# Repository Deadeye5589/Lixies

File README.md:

# Lixies
LED based Nixie style displays in different sizes

Based on the works of Connor Nishijima

A Lixie Clock consits of 4 or 6 units in either small or big version. An ESP8266 or ESP32 in combination with a DS3213 real time clock.

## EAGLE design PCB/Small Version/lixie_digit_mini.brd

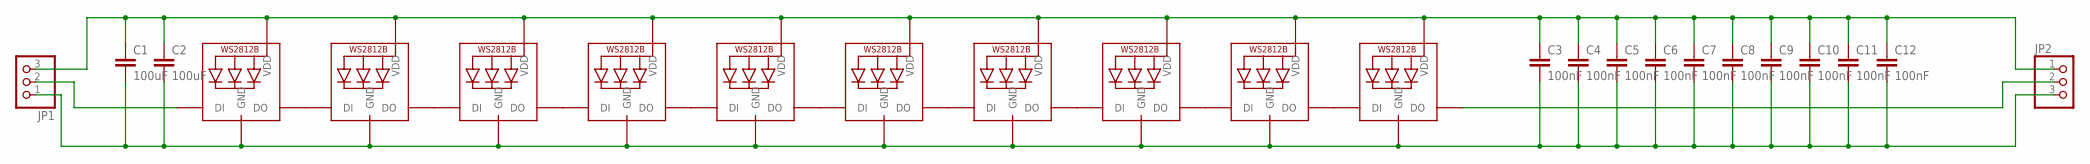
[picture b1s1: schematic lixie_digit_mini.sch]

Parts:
C1, C2: 100uF; C1206K
C3, C4, C5, C6, C7, C8, C9, C10, C11, C12: 100nF; C0805K
JP1, JP2: PINHD-1X3; 1X03
LED1, LED2, LED3, LED4, LED5, LED6, LED7, LED8, LED9, LED10: WS2812B5050; WS2812B

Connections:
GND: C1.2, C2.2, C3.2, C4.2, C5.2, C6.2, C7.2, C8.2, C9.2, C10.2, C11.2, C12.2, JP1.1, JP2.3, LED1.3-GND (GND), LED2.3-GND (GND), LED3.3-GND (GND), LED4.3-GND (GND), LED5.3-GND (GND), LED6.3-GND (GND), LED7.3-GND (GND), LED8.3-GND (GND), LED9.3-GND (GND), LED10.3-GND (GND)
unnamed: LED1.2-DOUT (DO), LED2.4-DIN (DI)
unnamed: LED2.2-DOUT (DO), LED3.4-DIN (DI)
unnamed: LED3.2-DOUT (DO), LED4.4-DIN (DI)
unnamed: LED4.2-DOUT (DO), LED5.4-DIN (DI)
unnamed: LED5.2-DOUT (DO), LED6.4-DIN (DI)
unnamed: LED6.2-DOUT (DO), LED7.4-DIN (DI)
unnamed: LED7.2-DOUT (DO), LED8.4-DIN (DI)
unnamed: LED8.2-DOUT (DO), LED9.4-DIN (DI)
unnamed: LED9.2-DOUT (DO), LED10.4-DIN (DI)
unnamed: JP1.2, LED1.4-DIN (DI)
unnamed: JP2.2, LED10.2-DOUT (DO)
VCC: C1.1, C2.1, C3.1, C4.1, C5.1, C6.1, C7.1, C8.1, C9.1, C10.1, C11.1, C12.1, JP1.3, JP2.1, LED1.1-VDD (VDD), LED2.1-VDD (VDD), LED3.1-VDD (VDD), LED4.1-VDD (VDD), LED5.1-VDD (VDD), LED6.1-VDD (VDD), LED7.1-VDD (VDD), LED8.1-VDD (VDD), LED9.1-VDD (VDD), LED10.1-VDD (VDD)

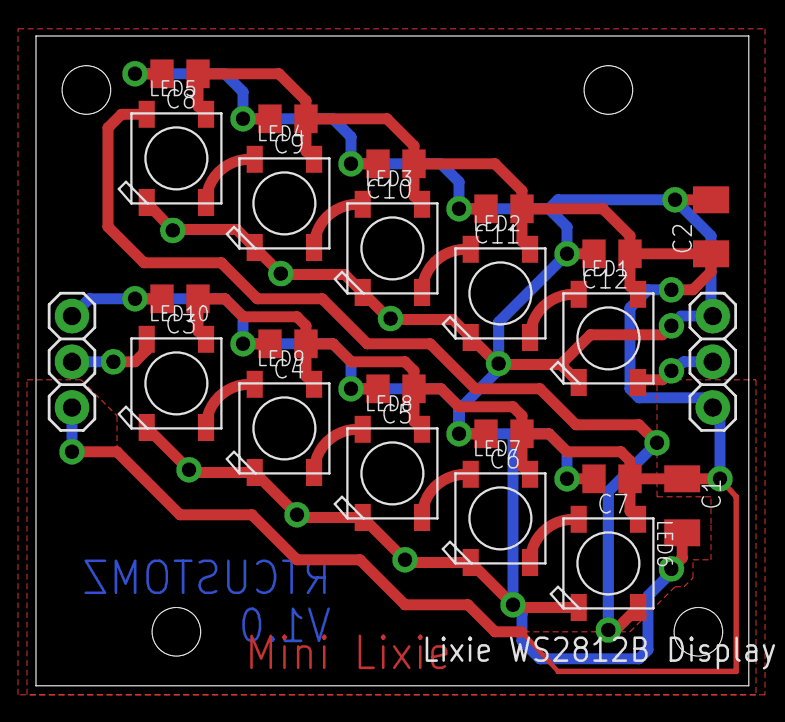
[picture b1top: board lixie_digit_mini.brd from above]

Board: 2 copper layers, 39.6 x 36.1 mm, 24 parts (0 on the bottom side), 13 nets.

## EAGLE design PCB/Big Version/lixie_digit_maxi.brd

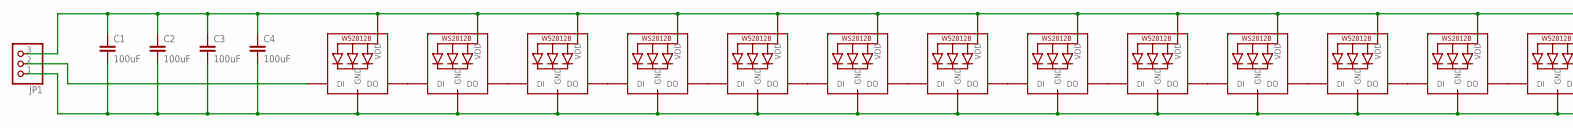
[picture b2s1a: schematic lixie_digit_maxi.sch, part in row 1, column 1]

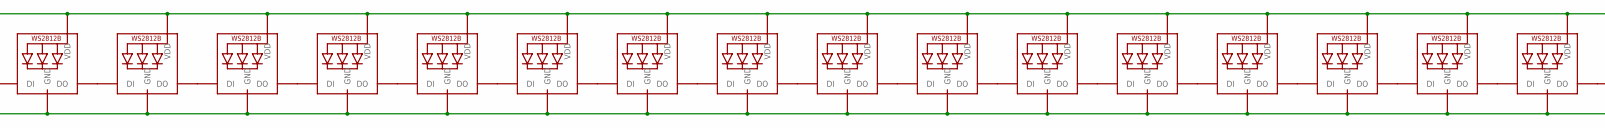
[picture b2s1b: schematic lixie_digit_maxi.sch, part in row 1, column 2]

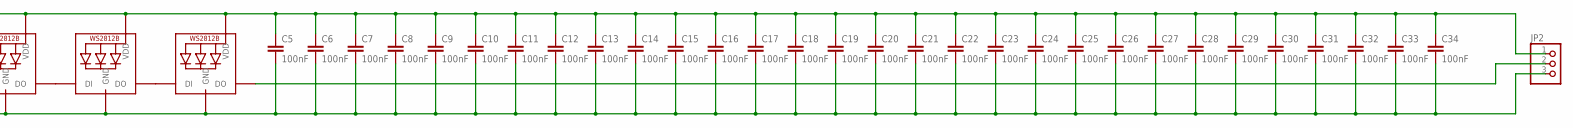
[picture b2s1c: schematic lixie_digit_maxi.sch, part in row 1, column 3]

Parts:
C1, C2, C3, C4: 100uF; C1206K
C5, C6, C7, C8, C9, C10, C11, C12, C13, C14, C15, C16, C17, C18, C19, C20, C21, C22, C23, C24, C25, C26, C27, C28, C29, C30, C31, C32, C33, C34: 100nF; C0402K
JP1, JP2: PINHD-1X3; 1X03
LED1, LED2, LED3, LED4, LED5, LED6, LED7, LED8, LED9, LED10, LED11, LED12, LED13, LED14, LED15, LED16, LED17, LED18, LED19, LED20, LED21, LED22, LED23, LED24, LED25, LED26, LED27, LED28, LED29, LED30: WS2812B5050; WS2812B

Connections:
GND: C1.2, C2.2, C3.2, C4.2, C5.2, C6.2, C7.2, C8.2, C9.2, C10.2, C11.2, C12.2, C13.2, C14.2, C15.2, C16.2, C17.2, C18.2, C19.2, C20.2, C21.2, C22.2, C23.2, C24.2, C25.2, C26.2, C27.2, C28.2, C29.2, C30.2, C31.2, C32.2, C33.2, C34.2, JP1.1, JP2.3, LED1.3-GND (GND), LED2.3-GND (GND), LED3.3-GND (GND), LED4.3-GND (GND), LED5.3-GND (GND), LED6.3-GND (GND), LED7.3-GND (GND), LED8.3-GND (GND), LED9.3-GND (GND), LED10.3-GND (GND), LED11.3-GND (GND), LED12.3-GND (GND), LED13.3-GND (GND), LED14.3-GND (GND), LED15.3-GND (GND), LED16.3-GND (GND), LED17.3-GND (GND), LED18.3-GND (GND), LED19.3-GND (GND), LED20.3-GND (GND), LED21.3-GND (GND), LED22.3-GND (GND), LED23.3-GND (GND), LED24.3-GND (GND), LED25.3-GND (GND), LED26.3-GND (GND), LED27.3-GND (GND), LED28.3-GND (GND), LED29.3-GND (GND), LED30.3-GND (GND)
unnamed: LED11.2-DOUT (DO), LED12.4-DIN (DI)
unnamed: LED12.2-DOUT (DO), LED13.4-DIN (DI)
unnamed: LED13.2-DOUT (DO), LED14.4-DIN (DI)
unnamed: LED14.2-DOUT (DO), LED15.4-DIN (DI)
unnamed: LED15.2-DOUT (DO), LED16.4-DIN (DI)
unnamed: LED16.2-DOUT (DO), LED17.4-DIN (DI)
unnamed: LED17.2-DOUT (DO), LED18.4-DIN (DI)
unnamed: LED18.2-DOUT (DO), LED19.4-DIN (DI)
unnamed: LED19.2-DOUT (DO), LED20.4-DIN (DI)
unnamed: LED20.2-DOUT (DO), LED21.4-DIN (DI)
unnamed: LED21.2-DOUT (DO), LED22.4-DIN (DI)
unnamed: LED22.2-DOUT (DO), LED23.4-DIN (DI)
unnamed: LED23.2-DOUT (DO), LED24.4-DIN (DI)
unnamed: LED24.2-DOUT (DO), LED25.4-DIN (DI)
unnamed: LED25.2-DOUT (DO), LED26.4-DIN (DI)
unnamed: LED26.2-DOUT (DO), LED27.4-DIN (DI)
unnamed: LED27.2-DOUT (DO), LED28.4-DIN (DI)
unnamed: LED28.2-DOUT (DO), LED29.4-DIN (DI)
unnamed: LED29.2-DOUT (DO), LED30.4-DIN (DI)
unnamed: LED10.2-DOUT (DO), LED11.4-DIN (DI)
unnamed: LED7.2-DOUT (DO), LED8.4-DIN (DI)
unnamed: LED6.2-DOUT (DO), LED7.4-DIN (DI)
unnamed: JP2.2, LED30.2-DOUT (DO)
unnamed: LED5.2-DOUT (DO), LED6.4-DIN (DI)
unnamed: LED3.2-DOUT (DO), LED4.4-DIN (DI)
unnamed: LED2.2-DOUT (DO), LED3.4-DIN (DI)
unnamed: LED1.2-DOUT (DO), LED2.4-DIN (DI)
unnamed: LED4.2-DOUT (DO), LED5.4-DIN (DI)
unnamed: LED8.2-DOUT (DO), LED9.4-DIN (DI)
unnamed: LED9.2-DOUT (DO), LED10.4-DIN (DI)
unnamed: JP1.2, LED1.4-DIN (DI)
VCC: C1.1, C2.1, C3.1, C4.1, C5.1, C6.1, C7.1, C8.1, C9.1, C10.1, C11.1, C12.1, C13.1, C14.1, C15.1, C16.1, C17.1, C18.1, C19.1, C20.1, C21.1, C22.1, C23.1, C24.1, C25.1, C26.1, C27.1, C28.1, C29.1, C30.1, C31.1, C32.1, C33.1, C34.1, JP1.3, JP2.1, LED1.1-VDD (VDD), LED2.1-VDD (VDD), LED3.1-VDD (VDD), LED4.1-VDD (VDD), LED5.1-VDD (VDD), LED6.1-VDD (VDD), LED7.1-VDD (VDD), LED8.1-VDD (VDD), LED9.1-VDD (VDD), LED10.1-VDD (VDD), LED11.1-VDD (VDD), LED12.1-VDD (VDD), LED13.1-VDD (VDD), LED14.1-VDD (VDD), LED15.1-VDD (VDD), LED16.1-VDD (VDD), LED17.1-VDD (VDD), LED18.1-VDD (VDD), LED19.1-VDD (VDD), LED20.1-VDD (VDD), LED21.1-VDD (VDD), LED22.1-VDD (VDD), LED23.1-VDD (VDD), LED24.1-VDD (VDD), LED25.1-VDD (VDD), LED26.1-VDD (VDD), LED27.1-VDD (VDD), LED28.1-VDD (VDD), LED29.1-VDD (VDD), LED30.1-VDD (VDD)

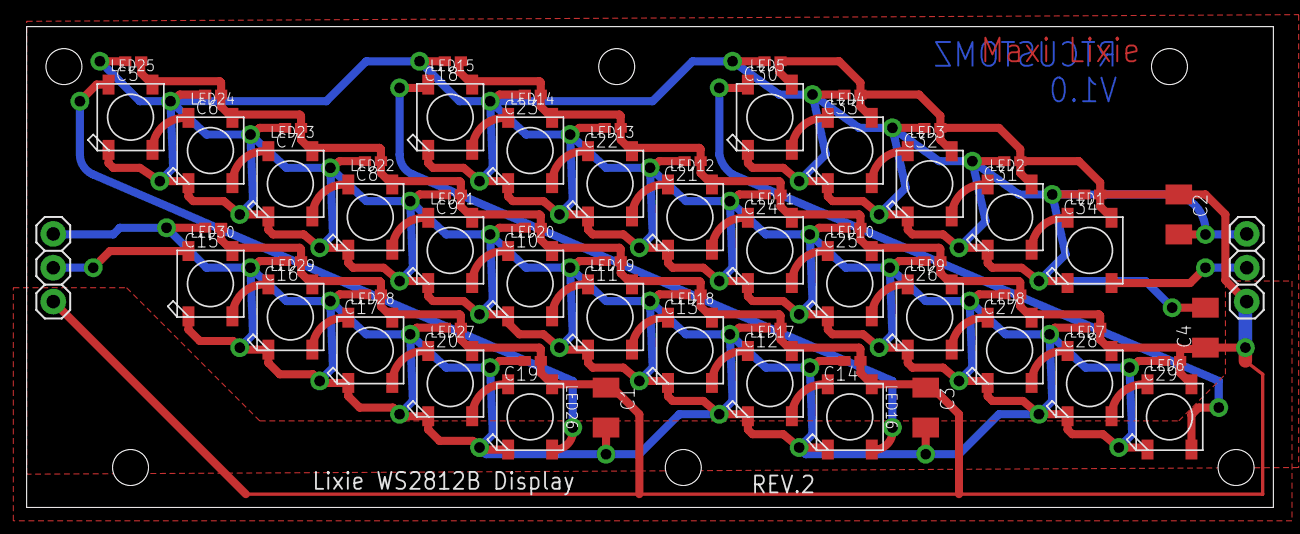
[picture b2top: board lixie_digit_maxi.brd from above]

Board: 2 copper layers, 93.6 x 36.1 mm, 66 parts (0 on the bottom side), 33 nets.

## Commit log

2018-11-24 V1 for LED PCB
    Small and Big Lixie PCBs
2018-11-24 PCB for Dots inbetween Numbers
    V1 of the Dots PCB
    Only 4 LEDs to enable multi layer color effects even if we only have dots
2018-11-24 Add files via upload
    Corrected an non rectengular cutout in the aperature layer
2018-11-25 Added Layer Halterung
2020-05-02 First somehow running version
    Get time via NTP
    Store time into DS3231 RTC
    Show time, while blink : each second
2020-05-02 Needed files from external sources
    Lixie lib based on the works of Connor Nishijima
    https://github.com/connornishijima/Lixie-arduino
    ntp functions based on the work of Stefan Thesen
    https://blog.thesen.eu/lokale-uhrzeit-mit-dem-esp8266-und-einem-ntp-zeitserver-inklusive-sommerwinterzeit/
2020-05-04 First somehow running Version
    Connects to WLAN
    Gets NTP Time
    Stores it into RTC
    Shows time
2020-05-04 Lib for displaying lixies
    Based on the work of Connor Nishijima
    https://github.com/connornishijima/Lixie-arduino
2020-05-04 NTP functions
    Based on the work of Stefan Thesen
    https://blog.thesen.eu/lokale-uhrzeit-mit-dem-esp8266-und-einem-ntp-zeitserver-inklusive-sommerwinterzeit/
2020-05-25 Lib working correct
    Lib working correctly now
    Added idle animatin while Wifi connects
2020-05-25 Update to new lib
    Reworked for Lixie II lib from Connor Nishijima
    Modified Lib to smaller LED ammount per digit
    Added Wifi connection timeout and fallback
2020-10-24 add basic webserver functionality
2020-10-24 change multiple strings to one website string function that is send later
2020-10-24 add different cpp/h files for better handling of Webserver
2020-10-25 add different cpp/h files for rtc functions
2020-10-28 add different cpp/h files for wifi and ntp functions
2021-01-26 seperate functions and add wifi interface
2022-03-18 Change Timer Server IP
    Old time server was not responding anymore. Changed to new server.
2022-03-18 Color change interval added
    Addes interval to change colors every 10 seconds
2022-03-18 Color change interval
    Addes interval to change colors every 10 seconds
2022-03-18 Color change interval
    Addes 10 seconds color change interval as demo.
    removed double lixie init during setup.

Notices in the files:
PCB/Big Version/lixie_digit_maxi.brd:
Released under the GPLv3 License
